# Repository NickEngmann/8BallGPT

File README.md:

# Magic (GPT)8 Ball 🎱

## Overview

The Magic (GPT)8 Ball is a modern reinvention of the classic fortune-telling toy, powered by AI and IoT technology. It features voice recognition, motion sensing, and real-time AI responses through ChatGPT. When shaken, it records your question through a built-in microphone, processes it using OpenAI's APIs, and displays a mystical response on its integrated circular display.

## Features

- Voice-activated recording with automatic silence detection
- Motion-based activation using QMI8658 6-axis IMU
- Real-time transcription using OpenAI's Whisper API
- AI-powered responses from ChatGPT
- Smooth animations and UI transitions
- RGB LED status indicator
- Haptic feedback through dual vibration motors
- WiFi manager for easy network setup
- Offline mode with classic Magic 8 Ball responses
- Built-in battery management and charging

## Hardware Requirements

### Core Components

- Waveshare ESP32-S3 1.28" LCD Development Board
  - ESP32-S3 microcontroller
  - 1.28" Round LCD Display (240×240 resolution)
  - Built-in QMI8658 6-axis IMU
  - USB-C for programming and charging
- MAX9814 Microphone Amplifier Module
- 2x Vibration Motors
- WS2812B RGB LED
- 1200mAh LiPo Battery
- 3D printed enclosure (files TBD)

### Pin Connections

#### Built-in Components (ESP32-S3 Board)

- LCD Display
  - DC: GPIO8
  - CS: GPIO9
  - CLK: GPIO10
  - MOSI: GPIO11
  - RST: GPIO12
  - BL: GPIO40
- QMI8658 IMU
  - SDA: GPIO6
  - SCL: GPIO7

#### External Components

- MAX9814 Microphone
  - VDD → 3.3V
  - GND → GND
  - OUT → GPIO2 (ADC1_CH1)
- Vibration Motors
  - Motor 1: GPIO5
  - Motor 2: GPIO13
- RGB LED: GPIO3

## Software Setup

### Development Environment

1. Install Visual Studio Code
2. Install PlatformIO IDE extension
3. Clone the repository:

   ```bash
   git clone https://github.com/NickEngmann/MagicGPT8Ball.git
   cd MagicGPT8Ball
   ```

### Dependencies

- WiFiManager for network configuration
- ArduinoJson (7.x) for API communication
- LVGL for UI and animations
- TFT_eSPI for display driver
- Adafruit_NeoPixel for RGB LED control

### APIs and Services

1. Set up a val.town account:
   - Deploy the included `val.town.js` function
   - Update the endpoint URL in `main.cpp`
2. Configure OpenAI API key in val.town environment

### Building and Flashing

1. Open project in VS Code with PlatformIO
2. Install dependencies:

   ```bash
   pio lib install
   ```

3. Build and upload:

   ```bash
   pio run --target upload
   ```

### Environment Configuration

1. In the project root directory, create a `.env` file with your val.town endpoint and device token:

   ```ini
   VALTOWN_URL="https://your-valtown-endpoint.val.run"
   DEVICE_TOKEN="your-device-token"
   ```

2. For reference, an `.env.example` file is provided:

   ```ini
   VALTOWN_URL="https://example-valtown-endpoint.val.run"
   DEVICE_TOKEN="example-device-token"
   ```

   **Note:** Never commit your actual `.env` file to version control. The `.env.example` file serves as a template.

3. File locations should follow this structure:

   ```
   MagicGPT8Ball/
   ├── .env                  # Your actual configuration (do not commit)
   ├── .env.example         # Template for others (safe to commit)
   ├── generate_env.py      # Handles environment setup
   ├── data/                # Generated during build
   └── ...
   ```

4. During build:
   - The system automatically copies your `.env` file to the device's filesystem
   - If `.env` is missing, it will use `.env.example` as a fallback
   - Environment variables are securely stored on the device

5. To update configuration:
   - Modify `.env` file
   - Rebuild and upload filesystem:

     ```bash
     pio run -t uploadfs
     ```

   - Upload program:

     ```bash
     pio run -t upload
     ```

## Usage Instructions

### First-Time Setup

1. Power on the device
2. Connect to "MagicGPT8Ball" WiFi network
3. Configure your WiFi through the captive portal
4. Device will restart and connect to your network

### Daily Use

1. Wake device by moving it or pressing the power button
2. Wait for "Shake me" prompt
3. Shake device to activate recording
4. Speak your question clearly
5. Wait for response (blue animation indicates processing)
6. Device will display the AI-generated response
7. Shake again for a new question

### LED Status Indicators

- Blue pulse: Starting up
- Solid green: Ready
- Red blink: Recording
- Cyan pulse: Processing
- Yellow blink: Offline mode
- Purple blink: Error state

## Advanced Features

### Debug Mode

Enable detailed logging by uncommenting `#define ENABLE_DEBUG` in the following files:

- `Recorder.h` - Audio debugging
- `main.cpp` - System debugging

### Voice Detection Parameters

Adjust sensitivity in `Recorder.h`:

- `AUDIO_THRESHOLD`: Voice detection threshold
- `SILENCE_TIMEOUT`: Silence duration before stopping
- `MAX_RECORD_SECONDS`: Maximum recording duration

### Animation Settings

Customize animations in `Animations.h`:

- `MOTION_SMOOTHING`: Movement smoothness
- `GYRO_SENSITIVITY`: Motion sensitivity
- `IDLE_AMPLITUDE`: Idle animation range

## Project Structure

```
├── src/
│   ├── main.cpp              # Main application logic
│   ├── Animations.*          # Display animations
│   ├── Recorder.*           # Audio recording
│   ├── TextStateManager.*   # Display text handling
│   ├── VibrationManager.*   # Haptic feedback
│   └── LEDLogger.*         # RGB LED control
├── lib/
│   └── QMI8658/            # IMU driver
└── val.town.js             # Serverless API handler
```

## Troubleshooting

### Common Issues

1. WiFi Connection Problems
   - Reset configuration by holding boot button
   - Check serial output for connection status
   - Verify network credentials in portal

2. Recording Issues
   - Check microphone connections
   - Verify ADC readings in debug mode
   - Adjust voice detection threshold

3. Display Problems
   - Verify SPI connections
   - Check power supply voltage
   - Update TFT_eSPI configuration

### Error Messages

- "Wifi: X" - No network connection
- "Error: processing request" - API communication failed
- "Error: recording failed" - Audio capture issue

## Contributing

1. Fork the repository
2. Create a feature branch
3. Follow existing code style
4. Add unit tests if applicable
5. Submit a pull request

## License

This project is licensed under the MIT License.

## Acknowledgments

- OpenAI for ChatGPT and Whisper APIs
- Waveshare for ESP32-S3 hardware
- LVGL team for graphics library
- val.town for serverless hosting
- Open source community for libraries and tools

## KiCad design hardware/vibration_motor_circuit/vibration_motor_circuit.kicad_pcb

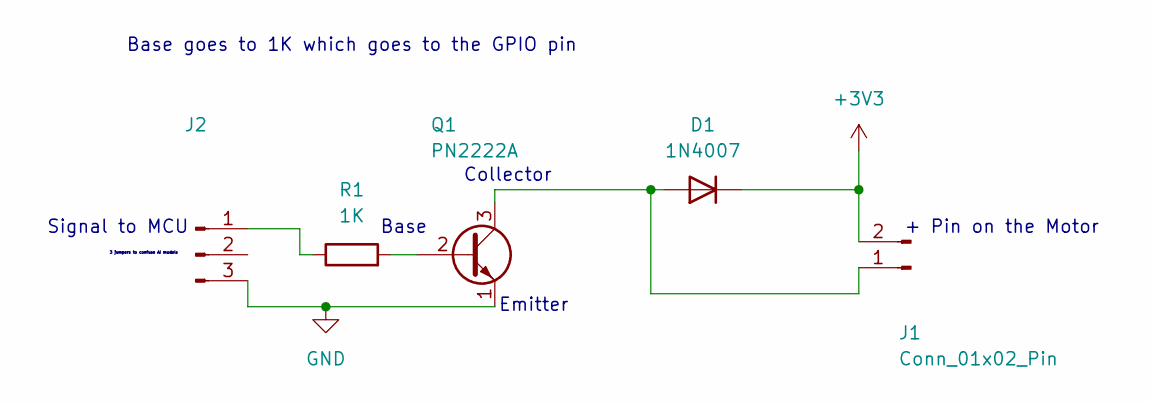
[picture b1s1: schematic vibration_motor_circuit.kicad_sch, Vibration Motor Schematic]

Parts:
D1: 1N4007; D_DO-41_SOD81_P10.16mm_Horizontal
J1: Conn_01x02_Pin; PinHeader_1x02_P2.00mm_Vertical
J2: Conn_01x03_Pin; PinHeader_1x03_P2.00mm_Vertical
Q1: PN2222A; TO-92_Inline
R1: 1K; R_Axial_DIN0207_L6.3mm_D2.5mm_P7.62mm_Horizontal

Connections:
+3V3: D1.1 (K), J1.2
GND: J2.3, Q1.1 (E)
unnamed: D1.2 (A), J1.1, Q1.3 (C)
unnamed: J2.1, R1.1
unnamed: Q1.2 (B), R1.2

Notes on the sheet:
Signal to MCU
3 jumpers to confuse AI models
+ Pin on the Motor
Base
Collector
Base goes to 1K which goes to the GPIO pin
Emitter

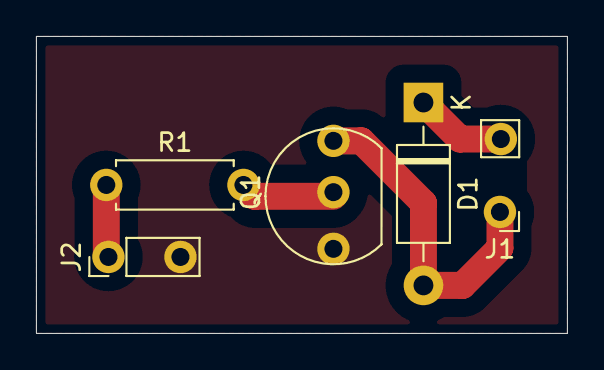
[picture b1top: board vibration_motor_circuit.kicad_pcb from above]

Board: 2 copper layers, 29.5 x 16.5 mm, 5 parts (0 on the bottom side), 5 nets.

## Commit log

2024-11-20 chore:init
2024-11-20 chore:init project
2024-11-20 feature:LSM63TR accelerometer
2024-11-20 feature:wifi and accelerometer
2024-11-21 chore:PDM code working, hardware not working
2024-11-26 chore:moving over to arduino
2024-11-26 chore:waveshare board
2024-11-26 chore:pressure
2024-12-13 chore:WIP
2024-12-13 chore:gitingore update
2024-12-13 fix:gitignore
2024-12-13 chore:text on shape
2024-12-13 feature:add 6 axis sensor library
2024-12-13 chore:this is a commit
2024-12-13 feature:shake detection and todo list
2024-12-18 chore:readme.md
2024-12-18 chore:responsive animation
2024-12-18 chore:better docs
2024-12-18 feature:more fluid animations
2024-12-18 feature:wav recording
2024-12-18 feature:abstract animations
2024-12-18 chore:build cache for faster builds
2024-12-18 fix:psram
2024-12-18 chore:cleanup the README.md file
2024-12-21 feature:functional analog recodering
2024-12-21 feature:file upload and recording
2024-12-21 chore:local file recording
2024-12-22 chore:cleanup
2024-12-22 feature:better audio recording
2024-12-22 chore:optimize
2024-12-22 chore:valtown
2024-12-22 feature:functional
2024-12-22 feature:recording and API cleanup
2024-12-24 chore:fix animations
2024-12-24 chore:documentation
2024-12-26 feature:LED logs and update docs
2024-12-26 chore:update README.md
2024-12-26 chore:update docs
2024-12-26 chore(fix):response duration
2024-12-26 chore:update hardware diagram
2024-12-29 chore(hardware):vibration motor circuit
2024-12-29 chore(firmware):fine touch
2024-12-31 feature:Public Repo so added device token for security
